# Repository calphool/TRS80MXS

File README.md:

# TRS80MXS
TRS-80 Modular eXpansion System

This is repo is for the TRS-80 Modular eXpansion System (MXS).  The intent is to make it the final of a series of 
prototypes (TRS80HDD and TRS80GS and a memory expansion module).  

The MXS consists of four modules set up as a stackable set.  So, you can build the base module first, which will 
give you a 32k memory expansion for your TRS-80 Model 1, as well as a power conditioning base that the other boards
use.  Then you can make either the floppy drive emulator, the TI video/graphics board, or the WIFI board (or all three).  
The boards snap together.  

Theory of Operation
===================

The basic theory of operation of the MXS is covered in the other projects in this repo.  The combined unit has a few 
unique characteristics.  First, it has three headers at the north, and south positions, and northeast of each board.  These 
are what allow the boards to be stacked.  One header is mostly the address bus of the TRS-80 expansion connector, 
passed through a 74LS244 buffer.  It also includes the operation signals (RD, WR, IN, OUT).  The opposite header 
contains the data bus and a few miscellaneous signals.  Finally the header at the northeast position is 4 lines that 
are OR-ed into the WAIT* signal as well as another 4 that are tied into the INTERUPT* signal.  This allows the 
MXS to host 4 separate chips that might use the WAIT* mechanism (as the sound chips and the floppy emulator 
flip flop do), and 4 interrupt chips (which presently are only used by the floppy emulator for its clock and 
drive activity interrupts).  The floppy emulator board also includes an 8x2 header that consolidates all the 
unused Teensy signals as well as a ground, 5V, and 3.3V signal.  These pins can be utilized to extend the functionality
of the Teensy unit.

Build Notes
===========

September 21, 2020

I've been fooling around with a few more designs recently.  Someone asked me if I had considered building a stand alone joystick board.
I had never considered it, but I went ahead and put two together.  One supports two joystick ports, and allows you to select the port 
numbers with dip switches.  The other is bare bones.  It only supports one joystick, but it can be built for somewhere between $15 and $30.

I also stumbled on a weird bug in the Teensy code for the floppy emulator.  When you swapped the disk image, every once in a while the 
TRS-80 would either lock up or show random garbage on the screen.  It looks like it's some kind of weird timing bug, most likely because 
the SD drive emulation is a little slow, and the code was leaving the WAIT signal low while the entire mount command was active.  So I 
tweaked a couple of things to fix that.

Also, just a quick note.  Jan Beta did a [Septandy video](https://www.youtube.com/watch?v=hyTF-FG4Bv8) where he's working on a Model 1.  He
didn't have a power supply for it, so he built one.  As I was watching the video, he briefly pulls out the schematic of the power supply, and 
I was like "Hey, that's *MY* power supply design!"  Unfortunately, he ends up losing a bunch of time in his debugging exercise because he 
didn't have one of the center tap lines connected correctly.  Incidentally, the way he constructed his power supply looks a lot more 
professional than mine.  I just threw mine in an electrical gang box, but his looks like it has a nice case and everything.

June 28, 2020

I updated the graphics/sound board again.  This time I made it so that the joystick ports are compatible with the "Alphastick" joystick
that was sold back in the early 1980s.  Several games support this joystick.  Also, I added a pair of jumpers that switches between the two 
different kinds of joystick trigger modes supported on these old joystick designs.  

I also learned how to use graphics mode 2 to produce near-bitmap style graphics.  So, I created a start-up screen for the MXS board that runs 
as soon as NewDos/80 loads up.

I finished the Pac-Man clone.  Now I've started on a Joust clone.  Joust runs in graphics mode 2, which makes for amazingly accurate reproduction of the 
background.  I've been working on the SDL emulation layer so that I can duplicate the TMS9918's "only 4 sprites per scanline" behavior.  I need to
duplicate this behavior so that I can come up with a "flicker routine."  This was the approach used for TMS9918 games back in the day.  You 
detect the situation, and then rotate the sprites' priorities in order to make sure that no one sprite turns off completely.

So I'm at version 1.4 of the graphics/sound board.  It's done and working well.  I have given some thought to removing two of the sound chips 
(do I really need 12 voices?  6 seems like it ought to be adequate), and replacing them with a TMS5220 speech synthesis chip.  This would make the 
board quite versatile.  Though the TMS5220 has become difficult to find, so I'm not sure.  I'll probably finish the Joust clone first.

May 9, 2020

Well, with the pandemic I've had a little time to work on the project some more.  I haven't worked on the wifi board recently,
but I decided to put together at least one piece of software that demonstrates the graphics/sound/gaming capabilities of the 
TRS80MXS.  [Here's a little video of the Pac-Man clone.](https://youtu.be/DzdaCiHI2xc)  It's a work in progress, but it's at least starting to look like a playable game.

January 1, 2020

Well, we're in the new house, and semi-settled.  Always a million things to do when you move to a new house.  
However, I've got a little time to begin working on the Wifi module again.  As luck would have it, I'm now living 
only a few blocks from my friend who started this little adventure.  Just for fun over Christmas, I had my younger 
daughter come play some of the games that are loaded on the HDD module.  I even hooked up the cassette port to 
an amplifier, and I connected the composite video out on my old TRS-80 to our big screen TV.  It's kind of 
amazing when you think about it -- that computer is 42 years old, and I can connect it to a brand new flat panel display.
My daughter laughed her head off at these "cheesy old games."  She said something like "Dad, how could you guys 
stand to play these silly things?  There's no color. They're like really bad rip offs of arcade games that weren't 
that great to begin with!"  The answer of course is pretty simple.  We had no choice, and we *thought* they were 
pretty cool games.  In fact, I'm still pretty amazed when I ran a couple of those games and the authors had managed 
to implement a sample playing routine into the game so that when it started it said something like "Ready Player One" 
and "Game Over".  I mean, seriously -- in 1977 somebody had figured out how to sample audio and misuse the audio 
cassette port to drive voice samples.  It may not be impressive to my 20 something daughter, but it's still pretty 
impressive to me.  Perspective I guess.

So I'll see if I can wrap up the Wifi module in the next few weeks.  It was intended to be a general purpose 
wifi module, but I'm running into some things that make me think that may not be practical / easy.  The main one is 
that the ESP32 designers didn't really imagine that someone would use their module for a general purpose HTTP client.
The issue is basically RAM constraints.  We take it for granted these days, but TLS security requires a *lot* of 
RAM to store a bunch of root certificates.  The code that implements the TLS stuff for my ESP32 module makes a 
rather huge assumption that you're going to have a single site that the module is going to talk to, so you don't
really even try to load a bunch of root certs into it.  You load one for the site your're going to be accessing.
That obviously doesn't work very well when you're trying to build a general purpose tool.  Now I *could* probably
implement a proxy in AWS or something, and then set up my ESP32 to work against that HTTP proxy, but I don't really 
want this hardware to be a slave to some stupid proxy running in AWS.  So, I'm at a bit of an impass.  I *may* be 
able to figure something out, but it'll require me to dig deeply into the TLS libraries for my ESP32, and basically 
rewrite a huge chunk of their code.... and who knows what the performance will be like.  The other possible route 
would be to do something like reduce the functionality of the Wifi module so that it just gives you access to a 
particular hosting site, like maybe DropBox, but that's a bit of a let down.  We'll see what I can come up with 
over the next few weeks.

October 21, 2019

I'm still working on the project.  Things have slowed down a bit over the past few months because my eldest daughter got married, 
my youngest daughter started college, and I'm selling my house.  Once I get settled in the new house I'll pick up the 
Wifi module again, which is the last one to get completely working.  It "sort of" works right now, but it's built around the 
ESP32 module and that thing is sort of a bugger to code for.

July 25, 2019

I purchased a TRS-80 Model 1 on Ebay, so I don't have to borrow my friend's any more.  Unfortunately, it didn't come with a 
power supply.  So, I designed one.  Maybe someone with a bad power supply can use my design.  Here's a pic of the [schematic.](img/powersupply.pdf?raw=true)
The schematic and board layout is in the eaglecad folder.  I didn't actually use the board layout.  I just hand wired everything for my supply, and put it 
inside an electrical utility box.  If you decide to make one of these, be very careful.  You'd working with 110V mains voltages, so you need to know what 
you're doing.  I'm not responsible if you electrocute yourself!)

July 7, 2019

Figured something out that's worth documenting.  For a long time I've thought that something was wrong with drive 3.  I was 
using NEWDOS/80 2.0 disk images in drive 0 (boot drive).  Apparently there's a command (PDRIVE) that changes how DOS handles
different drives.  The drive image I was using had the wrong settings for drive 3, and by dumb luck and coincidence had 
usable settings for the other 3 drives.  As soon as I changed drive 3's TI and TD settings, it started working properly, 
so there's nothing actually wrong with drive 3!

July 4, 2019

I just designed and uploaded the WIFI module.  It hasn't been built yet, and no software has been written, but the design is 
there.  I'll get the board and parts on order and see what we get.  Chances are it won't work right off the bat, but you 
never know.  I decided to design this board with a couple of nuances.  First, it is built around port IO rather than memory 
mapping.  Since the port numbers aren't really standardized on the TRS-80, I decided to make the address decoder selectable 
with 8 DIP switches, so any port between 0 and 255 can be chosen.  The other nuance is that I didn't use any GALs or CPLDs for 
the glue logic.  That should make this board a little easier to build than the graphics/sound board.

June 28, 2019

I wrote a utility (called "trs80mxs") that runs on the TRS-80 to manipulate the drive images that are stored on the MicroSD card.  Before this utility,
you had to do your manipulations from a Mac connected via USB.  Since that forced the MXS to be tethered, that didn't seem like a good long term solution.
So, I "stole" the address the TRS-80 uses for printers and turned it into a "general purpose communication buffer" between the Teensy and the TRS-80.  So,
the Teensy receives data, turns it into SD Card manipulation commands, and replies back with what happened.  So the trs80mxs command utility doesn't 
really do much -- it just sends commands to the printer address, and reads the response back through the same address, and prints it to the screen on 
the TRS-80.  With it you can list disk images that are on the SD card, mount them onto one of the 4 emulated drive slots, and list what is currently 
mounted.  I've also created a video of using the utility [here.](https://www.youtube.com/watch?v=PgaojUgeEG4)

June 16, 2019

I tweaked the Teensy code to support deleting and writing files now.  So now drives 1-3 work as perfect emulators for JV1 formatted files.  I still have no
idea why drive 4 acts flaky.  The code is literally identical.  It's got to be some bug in the Model 1 hardware behavior when you've got 4 floppies. I also
uploaded some more audio tools.  midiDump accepts a midi file and converts it to a large array that can be copy/pasted into one of the player files like 
bach.c and then compiled with z88dk to create a .cmd file.  It's a tiny bit buggy, but it more-or-less produces the right data.  One of these days I'll 
dig into what precisely is causing it to act a little flakey.

June 10, 2019

Improved the timing just a bit.  Hear the difference [here.](https://www.youtube.com/watch?v=ByLgBegGoTc)

May 31, 2019

I just uploaded a demo program that plays a J.S. Bach tune - Invention 13.  [Here's a video of it playing.](https://www.youtube.com/watch?v=8Pr8rdETvlA)  The player isn't 
quite perfect (some slight timing issues), but it's certainly recognizable.  I used a preprocessor that's located in the OSX code that reads a midi file and turns it into 
an array of structures.  This isn't quite ideal.  It would probably be better to merge the two so that the TRS-80 can directly play midi files.  I may go ahead and piece 
that together over the weekend if I can get the midifile cpp code to compile on z88dk (the compiler I'm using for the TRS-80).

May 27, 2019

I got some of the sound code working.  It took a while to figure out what was going on in playnote.c.  One of the big pains in 
the sound chips is that I wired the data lines backward due to strange labelling in the sound chip data sheets.  This requires 
you to think of the bits backward.  Anyway... got it working.  It's pretty cool hearing 12 simultaneous harmonious voices.

May 23, 2019

I am still using the previous version of the PCBs at this time.  I've removed one of the 7805 linear regulators and 
replaced it with a TRACO TSR2-2450 switching regulator.  It appears that the regulator is stable enough, which was one of 
the questions I had about those regulators.  It appears that they'll work okay.  I'll probably spend some time this weekend
working on software.  I'd like to get an audio demo up and working, then some video, and then I'll pivot to working on a 
wifi shield at some point in the near future.

April 21, 2019

I reworked the base board design and the graphics board design.  I'd added a switching supply for the 5V, but I left the 7805 in 
there as well, with a jumper to allow you to switch back and forth.  Since I don't know if the switching supply will be too noisy,
I figured I wanted to have something that I knew would work.  The reason I had to redesign the base power board was that I had 
some fuzzy thinking going on.  I had two 7805 regulators on the original board, with their outputs tied together.  For some reason
I was thinking that I could manage more current that way, but that's only true in a really crude and kind of useless way.  Basically
that configuration is a known antipattern.  What happens is the two 7805s sort of "fight" to see who's going to provide the 5V, one
wins, takes all the current, overheats, and then the other suddenly jumps in if its sibling's heat overload kicks in.  That's not 
really useable.  So instead, I figured I'd switch to a higher amperage switching circuit built around an LM2596.  Since I don't know
if the noise will be too much, I left one of the 7805s in place, and made it so you could use a jumper to switch between the two.  

All of that got me to thinking that maybe having a "regulator board" wasn't such a dandy idea anyway.  It forces all the current 
to be fed from that one board, which in turn creates a heat problem if I use linear regulators.  So, I also ran the raw 9V in to 
one of the previously unused header pins, which means that in future designs the shields could regulate their own power if need be.
I probably should swap out all the 74LS* chips for 74HCT* chips to reduce power consumption.  Save the planet man.  What are you 
doing with all these old power hungry chips?  (My experience has been that 74LS* chips are rock solid at the design stage, and then 
you can pivot to HCT or ACT later to get additional desirable qualities -- you just have to sort of "ease" them into your design 
to make sure you don't get caught with some unexpected behavior difference -- sometimes related to timing.)

Additionally, I added some inductors to the graphics board.  These are on the TI-99/4A schematics for the VDP, and presumably they're
there to stabilize power.  I noticed that the TI-99/4A circuits have several of these chokes throughout, and there's a clean 
separation between normal VCC and VCC for video, with the chokes being the main difference.  So far I haven't needed these, but 
I figure the TI engineers probably had them there for some reason.

I've been working on some audio software.  Soon I think I'll have a 12-part harmony audio player.  It's sort of like a MOD tracker
from back in the day, but it doesn't play samples -- just manipulates the tone generators on the sound chips.  I'm anxious to 
get it working fully so I can try out some stuff.  I'll probably build some kind of midi converter as well.  Interestingly 
enough I haven't yet been able to find a midi file that tries to use 12 voices at once.  I wrote a little utility that calculates 
tone depth across all midi channels, ran hundreds of midi files through it, and so far I've only been able to find one song with 
more than 10 simultaneous voices, so 12 tonal voices might have been overkill.  Oh well.  ;-)

April 13, 2019

Got the third board working.  Getting the GAL22V10D programmed ended up being a pain.  I don't know why, but my VS4800 programmer just decided 
it wasn't going to program my ATF22V10C chips, so I bought some GAL22V10D chips.  It wouldn't program them either.  So, I decided to install VSpeed
(the programmer software) on another machine, and although at first it did the same thing, after fooling around over and over again (using the "all compare" function seemed to somehow cause it to start working).  One thing I can say for sure using that software and programmer is that until you issue the program instruction followed by a Read IC instruction and the checksum matches, you haven't programmed it properly.  You can also avoid the encrypt function, because it introduces its own chaos into the mix.  I suppose if I had an expensive programmer I wouldn't have to deal with that nonsense.

So, today is basically the culmination of a lot of hard work for a long time.  Today I should be able to write code on my Mac, create a disk image with trstools, sneakernet that code over a microSD card to my floppy emulator or upload it via USB to the teensy, and now I've got 12 channel audio and graphics (and of course 32k of extra ram on the power distribution board).  I'll go through a few cycles of that in the next few days to prove that it works, maybe create a build pipeline for my pacman game.  

I'll decide after I get a few rounds of that under my belt if I want to design/build one more shield board -- an ESP32 board.  This would give the system 
one additional feature that could be pretty useful -- wireless connectivity.  For my build pipeline that would make it so I could skip the sneakernet 
step, do a compile on the computer and transfer wirelessly (maybe -- I would have to figure out how to get the data over to the teensy.  Maybe some transfer program that would move data from the ESP32 to the Teensy.)

March 17, 2019

Happy St. Patrick's Day!  Got the redesigned drive emulator "shield" working.  Last board is the video/sound board.  There's some LED weirdness going on with
the drive emulator board (probably pin reassignments or something), but I'm not going to fool around with that right now.  The drive emulation works as 
expected, so that's good enough.  Stay tuned for the final board.  It has the most dramatic changes, so it may take a little more debugging to get fully 
working.  Once it's done, then our layer sandwich is basically done, except for the wireless board that I haven't yet designed. 

In totally unrelated news, I bought an Apple IIGS for $250.  I don't have boot disks, so it tries to boot and then complains that it has nothing to 
boot from.  I've ordered some disks from ebay.  Gotta love the IIGS.  It was Woz's last serious involvement in engineering at Apple, and some argue that it 
saved the company because it extended the aging Apple II line just long enough for Apple's board to realize that Jobs didn't know what he was talking about 
trying to push the Mac line when the technology just wasn't there yet.  Some people slather a lot of praise on Jobs, and certainly he was a visionary, but
his visions were often too far ahead of what the technology could do at the time, which put the company at risk in the late 80s.  Vision is great and 
necessary, but engineering is where the rubber meets the road.  Any science fiction writer can imagine amazing technology.  Making it actually happen 
requires hard skills.

March 3, 2019

I got the first instance of the base board built and tested.  It had a bug in the RD*, WR*, IN*, and OUT* signal lines.  I just started using 
[busses in EagleCad](./img/bus.gif?raw=true), and the user interface is incredibly awkward.  It's *super* easy to accidentally combine bus lines in weird ways.  In my case 
I had combined the buffered and unbuffered copies of the RD*, IN*, OUT*, and WR* lines, and it was creating havoc.  Even after removing the 74LS244
that was supposed to be doing the buffering, it was still screwing stuff up.  So I had to cut several traces around the chip and wire it properly.
I updated the design in EagleCad (it's now version 1.1), but didn't send for new boards at this point.  If someone wants to buy a few of these things 
or something I'll go ahead and order some more.  [Here's a pic of the completed board](./img/TRS80MXS_Base_v1.0.jpg?raw=true)... well, mostly.  I didn't have a 3.3v regulator handy, so I left that off for now, easy enough to solder in later when needed.  I also didn't have 4.7k resistor networks of the right size, so I cobbled together a hand full of discrete resistors and made an array out of them.  It's not pretty, but it's functional for now.  I also modified a switch to be a right angle mounted switch, which is a little kludgy but it's stable and will be hidden in plastic at some point anyway.  So yeah, not beautiful, but completely functional and I'll be able to build the other two "shield" modules and snap them on there.  Next I'll get the floppy emulator moved into this new form factor and tested.

Oh yeah, talking to my friend about the project, he expressed that he'd like to be able to browse the web with his TRS-80.  That's a bit o a tall order, 
but in theory would be possible with one more "shield".  Namely, an ESP32-based shield that was interfaced in the same way that the floppy emulator is 
interfaced (with a memory location peep hole mapping via a flip-flop and some latches, along with a WAIT* pin to aid in timing.)  So yeah, I may do that 
as well.  That'd make for quite the [sandwich](./img/sandwich.jpg?raw=true) of boards (base + graphics/sound + ESP32 wifi + floppy if we want to use it more than once), but in principle it would work.  The hardest part would be the browser rendering engine itself.  It might be one of those projects where
you can get the skeleton of the thing working fairly easily (basic text handling like a Lynx or maybe Browsh browser), and then graphics and sound would require a lot of design, which can turn into someone else's labor of love if they want.

February 22, 2019

I received my PCBs the other day.  Unfortunately I didn't do a great job of carefully reviewing them before sending them to the fab house.  There are 
so many little things to check when you're making a PCB that it's easy to miss something.  In this case, I didn't double (and triple) check the 
orientation of the headers on the boards.  I had them oriented correctly on the base and the floppy emulator PCB, but I didn't have them right on the 
sound/graphics board.  So, I had to flip them (both horizontally and vertically... wow was I off!), and then move everything around on the board 
because all the traces were now too far away from their respective chips.  *sigh*.  Oh well, I'll remember next time.  So now that's done and I've 
got the graphics/sound board headed back to the fab house.  I wish I could get some kind of deal on the shipping.  The cost of the fabrication is 
nothing ($5 for five boards), but the shipping is $20.  I can start populating the base and floppy PCBs now, so I'll probably do that this weekend.  One
of the cool things about these boards is that by making them modular like this, I think I should be able to use them on other 8-bit computers... basically
the base board will be unique to each computer, but the sound/graphics and floppy emulator may be pretty close to just working as a "cartridge" in 
other 8-bit PCBs of the era.  Of course, they'll need different software, but I don't think it'll be a total overhaul to get them working with say 
an Apple II, Commodore, or Atari 8-bit.  We'll see.  I mean, there will be differences because those computers were built around a 6502 and these 
cards were built for a Z80 machine, but a lot still translates -- an address bus, an 8-bit data bus, and so on.  We'll see when we get there.  If I 
keep plugging away I'm sure we can figure out a way to create a set of semi-universal cards... though maybe that's more of a long term goal.

February 9. 2019

Found [this interesting diagram.](https://www.kguttag.com/wp-content/uploads/2017/11/198x-External-Video-by-KG.pdf)  It may be worth digging into this later.  It would be kind of cool to be able to merge the TRS-80 
video signal with the TMS9918 signal such that the TRS-80 signal is the back plane.

February 8, 2019

I decided to add two more sound chips to the graphics/sound shield.  So now there should be a grand total of 12 tonal voices
and 4 noise / drum voices.  That will make the sound card significantly more capable than it was before.  I also decided 
to add a divide-by-four circuit to the second set of sound chips' clock.  So, they'll play at exactly 1/4 the pitch of the other 
two sound chips, making the bottom attainable frequency something like 27hz, which is around the bottom A of a piano keyboard, 
thereby fixing one of the terminal annoyances of the SN76489, its ridiculously large range that unfortunately tends to 
start in the middle of the keyboard with the standard clock frequency.

In order to add the extra sound chips, some surgery was necessary on all three boards.  I needed to change the base board 
to accommodate more wait signals, which in turn meant that I needed to add an 8-input NAND, which in turn meant that the
4-input NANDs I was using before were sort of redundant.  So now there are 8 available interrupt lines and 8 wait lines, in a 
4x4 pin grid at the north east side of the board.  Five wait signals are being used now (4 for sound and one for the 
floppy drive).  One interrupt is being used by the floppy emulator, and I've made the video interrupt optional with a jumper.
I don't think that interrupt will ever be especially useful (since the floppy drive interrupt occurs 25 times a second 
anyway, we might as well just poll the video card for anything we need), so making it optional seemed smart.

In order to add the extra sound chips I had to dispose of the ability to issue a VDP reset from software (needed the pins 
on the CPLD).  Also, I had to reorder a couple of the pins on the CPLD because for some reason one of the pins couldn't handle the 
complexity of the logic equation I was feeding it.  (Wouldn't compile in WinCupl.)

I'm thinking maybe at some point I'll throw together a MIDI player for this sound card.  With 12 voices and a full keyboard range and 
then some, I should be able to play practically anything.  Who knows, maybe with a little clever programming I'll be able to get some 
different timbres and be able to handle MIDI program change messages even.  12-part audio is better than some polyphonic synthesizers, 
so this should be interesting.  The only concern I have is the amount of data I'd be jamming down the bus to accomplish anything interesting.
Each tone change is two OUT instructions, so to play 12 voices at the same time you'd be executing 24 instructions.  I'm not sure
if the time gap between the first note and the last will be audible or not.  I hope not.

So, now I think I'm about ready to send these things to a fab house.  

February 3, 2019

Completed design of all three units.  Now cross checking them and preparing them for production at allpcb.com.

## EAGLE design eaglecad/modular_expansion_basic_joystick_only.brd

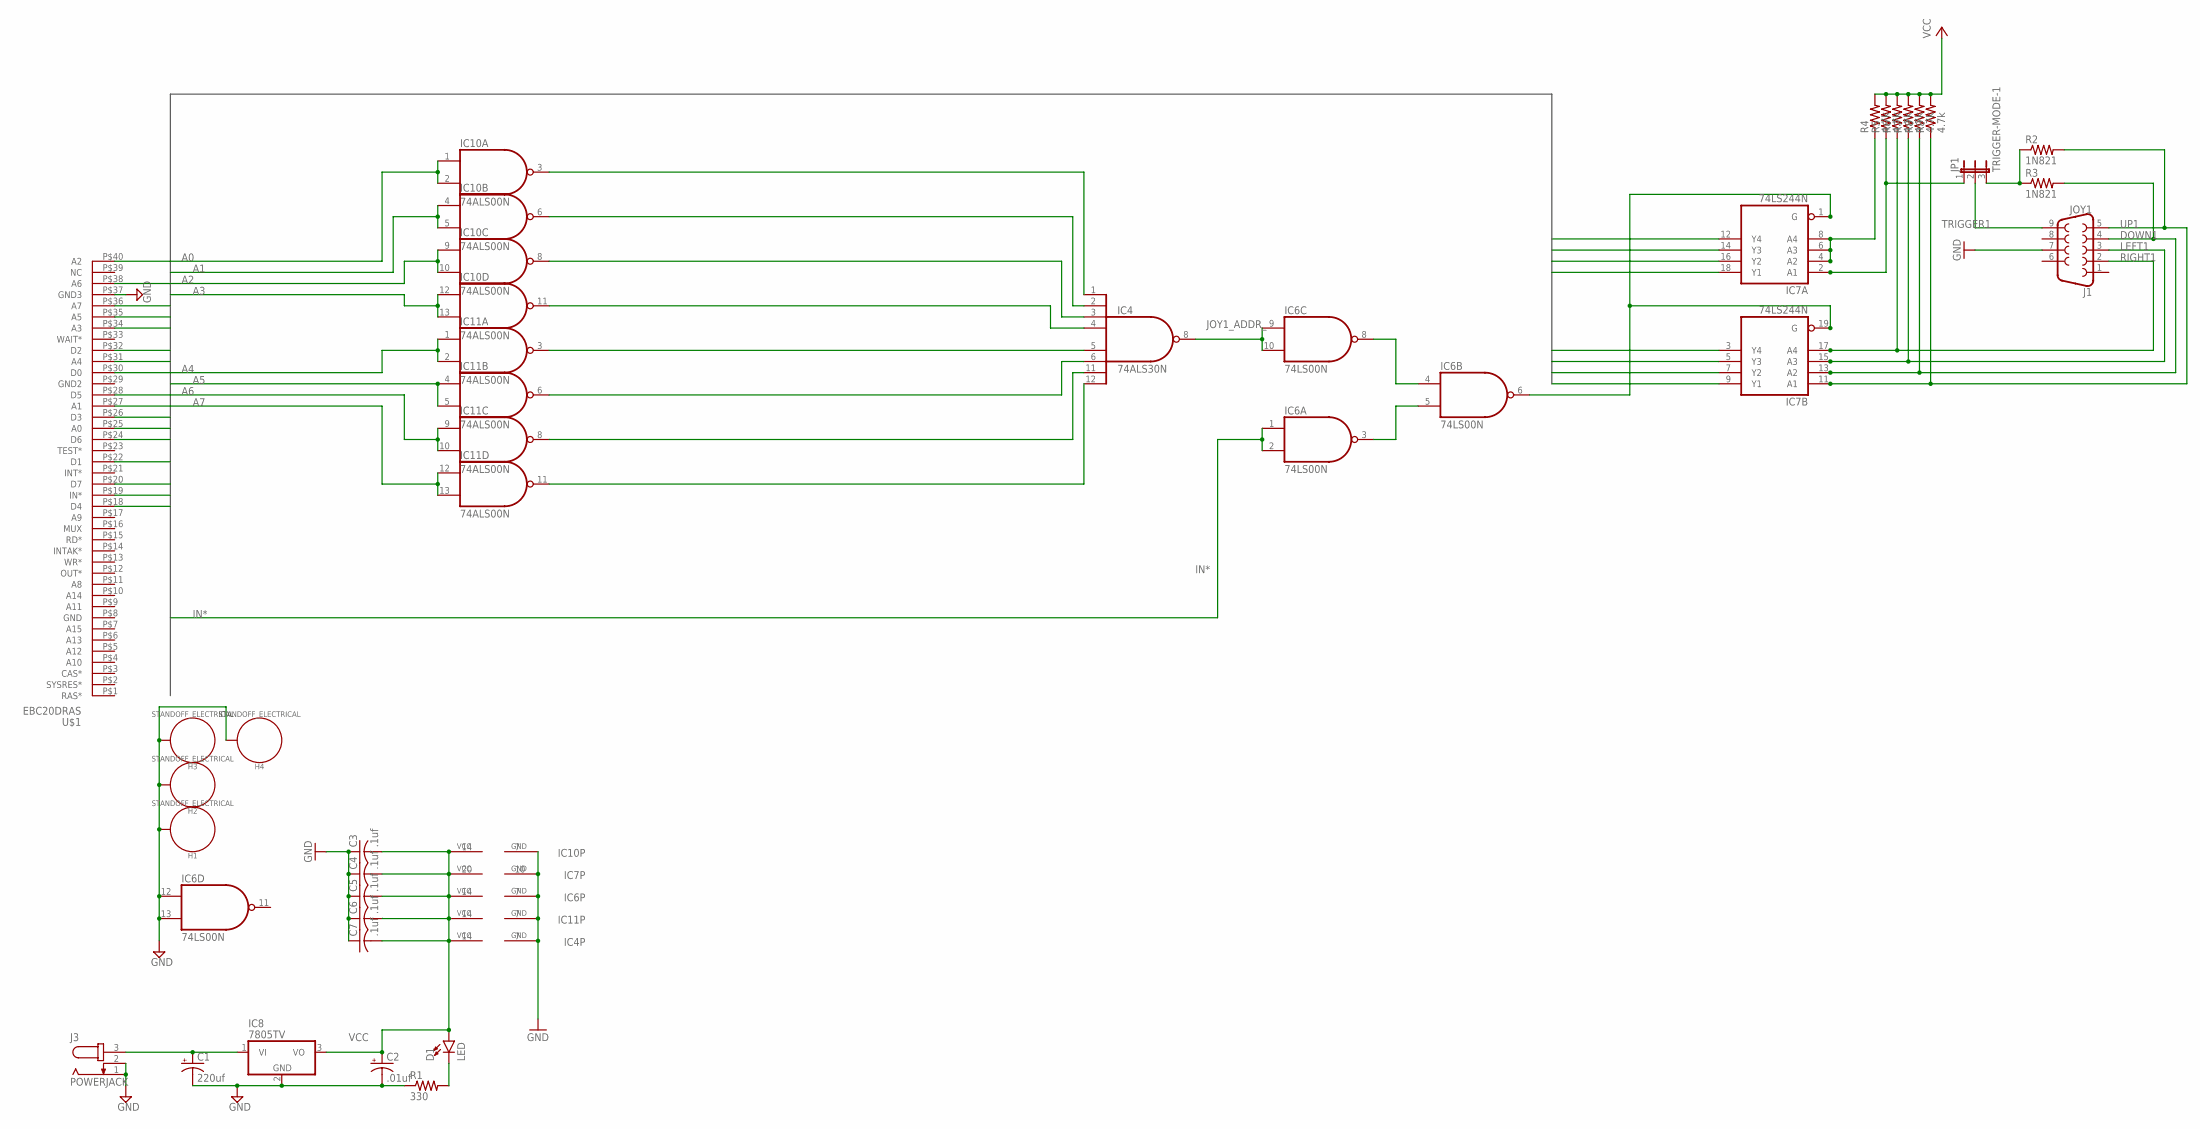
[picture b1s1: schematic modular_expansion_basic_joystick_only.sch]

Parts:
C1: 220uf; E3,5-10
C2: .01uf; E2,5-6E
C3, C4, C5, C6, C7: .1uf; C025-025X050
D1: LED; LED_3MM
H1, H2, H3, H4: STANDOFF_ELECTRICAL; STANDOFF-ELECTRICAL
IC4: 74ALS30N; DIL14
IC6: 74LS00N; DIL14
IC7: 74LS244N; DIL20
IC8: 7805TV; TO220V
IC10, IC11: 74ALS00N; DIL14
J1: JOY1; DB9
J3: POWERJACK; SPC4077
JP1: TRIGGER-MODE-1; JP2
R1: 330; 0204V
R2, R3: 1N821; 0204V
R4, R5, R6, R7, R8, R9: 4.7k; 0204/5
U$1: EBC20DRAS

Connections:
A0: IC10.1 (I0), IC10.2 (I1), U$1.P$25 (A0)
A1: IC10.4 (I0), IC10.5 (I1), U$1.P$27 (A1)
A2: IC10.9 (I0), IC10.10 (I1), U$1.P$40 (A2)
A3: IC10.12 (I0), IC10.13 (I1), U$1.P$34 (A3)
A4: IC11.1 (I0), IC11.2 (I1), U$1.P$31 (A4)
A5: IC11.4 (I0), IC11.5 (I1), U$1.P$35 (A5)
A6: IC11.9 (I0), IC11.10 (I1), U$1.P$38 (A6)
A7: IC11.12 (I0), IC11.13 (I1), U$1.P$36 (A7)
D0: IC7.9 (Y1), U$1.P$30 (D0)
D1: IC7.7 (Y2), U$1.P$22 (D1)
D2: IC7.5 (Y3), U$1.P$32 (D2)
D3: IC7.3 (Y4), U$1.P$26 (D3)
D4: IC7.18 (Y1), U$1.P$18 (D4)
D5: IC7.16 (Y2), U$1.P$28 (D5)
D6: IC7.14 (Y3), U$1.P$24 (D6)
D7: IC7.12 (Y4), U$1.P$20 (D7)
DOWN1: IC7.13 (A2), J1.4, R3.2, R8.1
GND: C1.-, C2.-, C3.1, C4.1, C5.1, C6.1, C7.1, H1.P1, H2.P1, H3.P1, H4.P1, IC4.7 (GND), IC6.7 (GND), IC6.12 (I0), IC6.13 (I1), IC7.10 (GND), IC8.2 (GND), IC10.7 (GND), IC11.7 (GND), J1.7, J3.1, J3.2, R1.1, U$1.P$37 (GND3)
IN*: IC6.1 (I0), IC6.2 (I1), U$1.P$19 (IN*)
JOY1_ADDR_: IC4.8 (O), IC6.9 (I0), IC6.10 (I1)
JOY1_SELECTED_: IC6.6 (O), IC7.1 (G), IC7.19 (G)
LEFT1: IC7.15 (A3), J1.3, R7.1
unnamed: IC4.5 (I4), IC11.3 (O)
unnamed: IC4.1 (I0), IC10.3 (O)
unnamed: IC4.6 (I5), IC11.6 (O)
unnamed: IC4.11 (I6), IC11.8 (O)
unnamed: IC4.2 (I1), IC10.6 (O)
unnamed: IC4.3 (I2), IC10.8 (O)
unnamed: IC4.12 (I7), IC11.11 (O)
unnamed: IC4.4 (I3), IC10.11 (O)
unnamed: IC6.4 (I0), IC6.8 (O)
unnamed: IC6.3 (O), IC6.5 (I1)
unnamed: C1.+, IC8.1 (VI), J3.3
unnamed: JP1.3, R2.1, R3.1
unnamed: D1.K (C), R1.2
unnamed: IC7.4 (A2), IC7.6 (A3), IC7.8 (A4), R4.1
unnamed: IC7.2 (A1), JP1.1, R5.1
RIGHT1: IC7.17 (A4), J1.2, R6.1
TRIGGER1: J1.9, JP1.2
UP1: IC7.11 (A1), J1.5, R2.2, R9.1
VCC: C2.+, C3.2, C4.2, C5.2, C6.2, C7.2, D1.A, IC4.14 (VCC), IC6.14 (VCC), IC7.20 (VCC), IC8.3 (VO), IC10.14 (VCC), IC11.14 (VCC), R4.2, R5.2, R6.2, R7.2, R8.2, R9.2

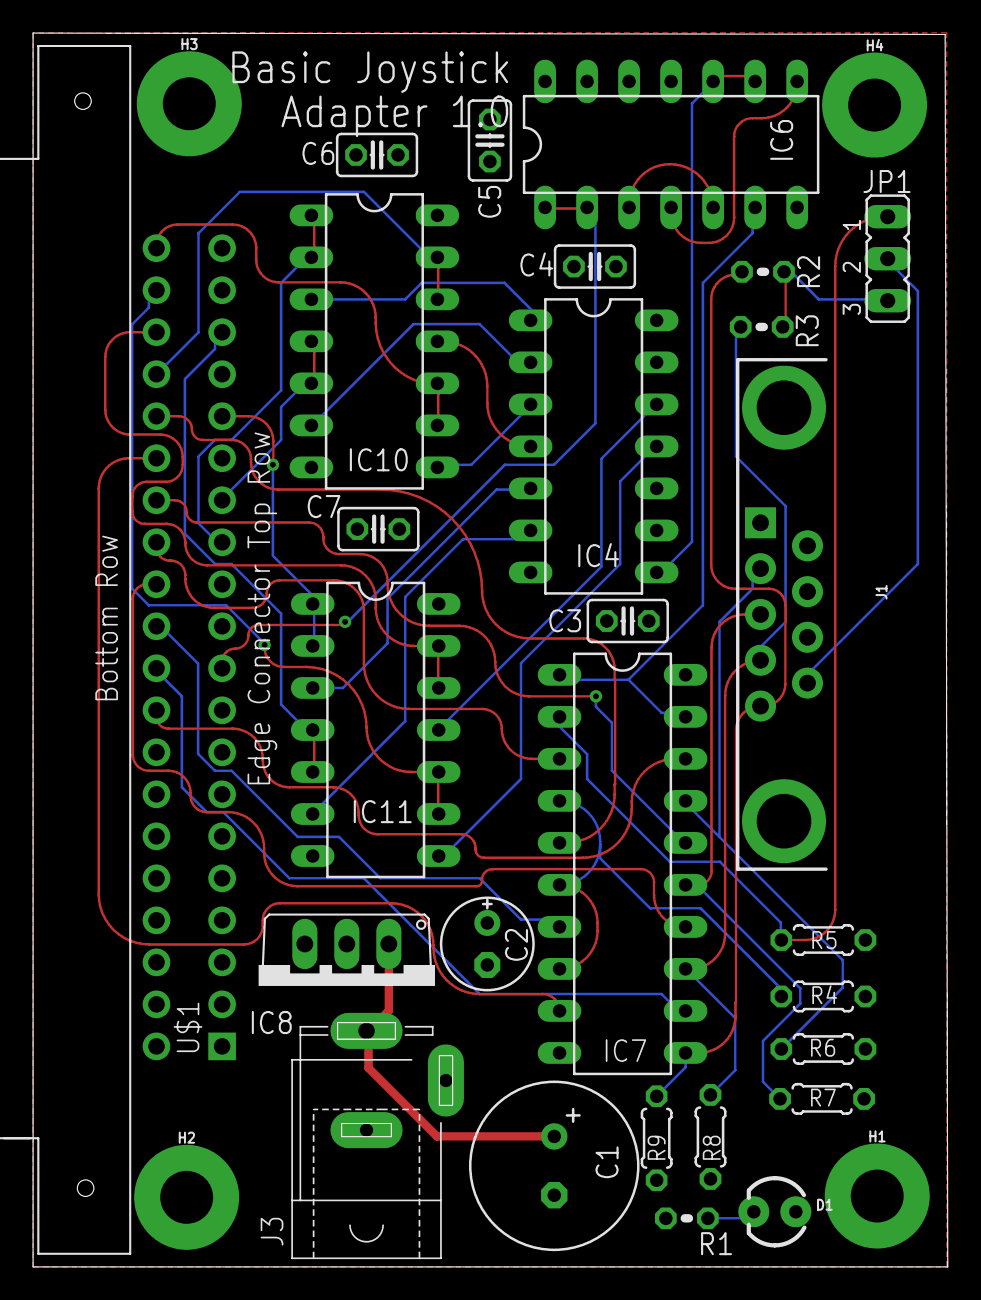
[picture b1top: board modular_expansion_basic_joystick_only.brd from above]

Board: 2 copper layers, 55.3 x 74.6 mm, 31 parts (0 on the bottom side), 41 nets.

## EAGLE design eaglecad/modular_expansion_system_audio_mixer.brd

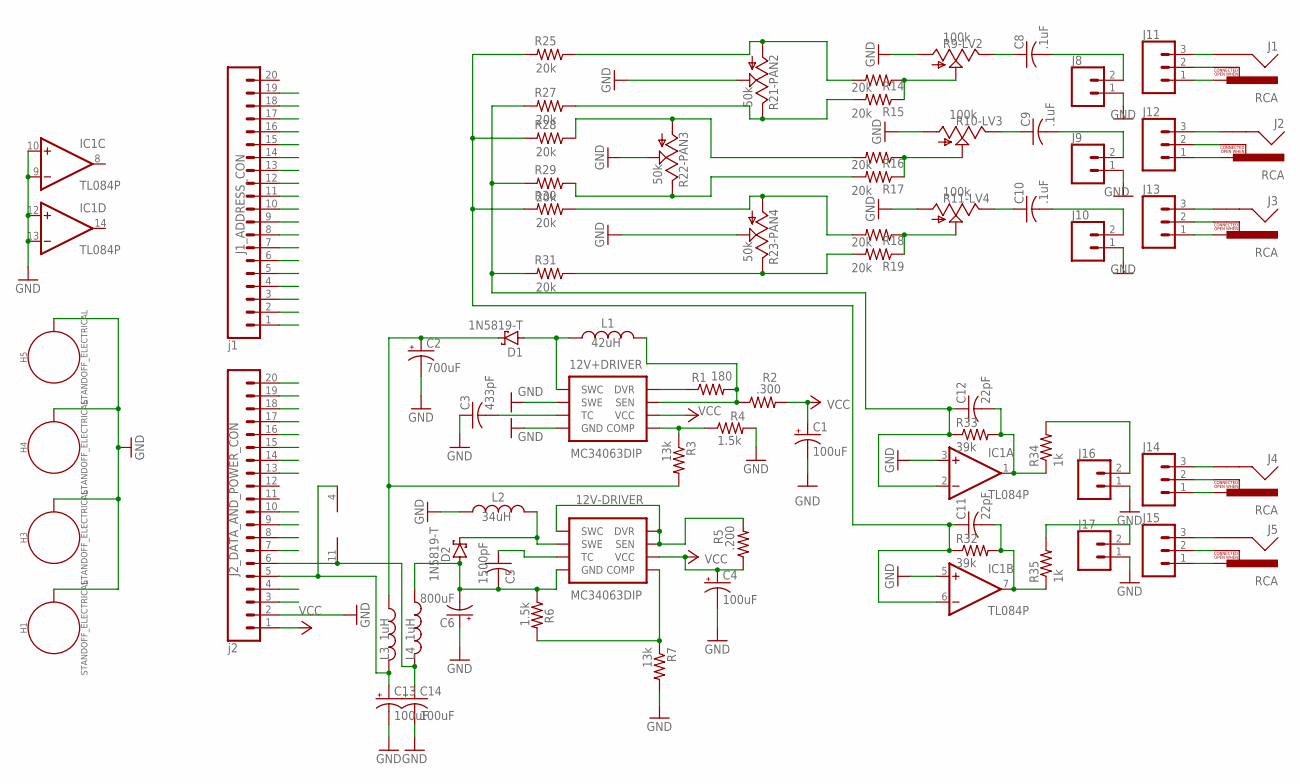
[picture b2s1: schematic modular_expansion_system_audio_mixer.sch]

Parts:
12V+DRIVER, 12V-DRIVER: MC34063DIP; DIP-08
C1, C4, C13, C14: 100uF; E2,5-5
C2: 700uF; E3,5-10
C3: 433pF; C025-040X050
C5: 1500pF; C025-040X050
C6: 800uF; E3,5-10
C8, C9, C10: .1uF; C025-024X044
C11, C12: 22pF; C025-024X044
D1, D2: 1N5819-T; DO41-7.6
H1, H3, H4, H5: STANDOFF_ELECTRICAL; STANDOFF-ELECTRICAL
IC1: TL084P; DIL14
J1, J2, J3, J4, J5: RCA
J1_ADDRESS_CON: j1; 1X20
J2_DATA_AND_POWER_CON: j2; 1X20
J8, J9, J10, J16, J17: CONN_02; 1X02
J11, J12, J13, J14, J15: CONN_03; 1X03
L1: 42uH; 0207/7
L2: 34uH; 0207/7
L3, L4: 1uH; 0207/5V
R1: 180; 0204V
R2: .300; 0204V
R3, R7: 13k; 0204V
R4, R6: 1.5k; 0204V
R5: .200; 0204V
R9-LV2, R10-LV3, R11-LV4: 100k; B25U
R14, R15, R16, R17, R18, R19, R25, R27, R28, R29, R30, R31: 20k; 0204V
R21-PAN2, R22-PAN3, R23-PAN4: 50k; B25U
R32, R33: 39k; 0204V
R34, R35: 1k; 0204V

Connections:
+12V: C2.+, D1.C, L3.1, R3.2
+12V_FILTERED: C13.+, IC1.4 (V+), J2_DATA_AND_POWER_CON.5, L3.2
-12V: 12V-DRIVER.4 (GND), C5.2, C6.-, D2.A, L4.1, R6.1
-12V-FILTERED: C14.+, IC1.11 (V-), J2_DATA_AND_POWER_CON.6, L4.2
A0: J1_ADDRESS_CON.1
A1: J1_ADDRESS_CON.2
A2: J1_ADDRESS_CON.3
A3: J1_ADDRESS_CON.4
A4: J1_ADDRESS_CON.5
A5: J1_ADDRESS_CON.6
A6: J1_ADDRESS_CON.7
A7: J1_ADDRESS_CON.8
A8: J1_ADDRESS_CON.9
A9: J1_ADDRESS_CON.10
A10: J1_ADDRESS_CON.11
A11: J1_ADDRESS_CON.12
A12: J1_ADDRESS_CON.13
A13: J1_ADDRESS_CON.14
A14: J1_ADDRESS_CON.15
A15: J1_ADDRESS_CON.16
CAS*: J2_DATA_AND_POWER_CON.9
D0: J2_DATA_AND_POWER_CON.20
D1: J2_DATA_AND_POWER_CON.19
D2: J2_DATA_AND_POWER_CON.18
D3: J2_DATA_AND_POWER_CON.17
D4: J2_DATA_AND_POWER_CON.16
D5: J2_DATA_AND_POWER_CON.15
D6: J2_DATA_AND_POWER_CON.14
D7: J2_DATA_AND_POWER_CON.13
GND: 12V+DRIVER.2 (SWE), 12V+DRIVER.4 (GND), C1.-, C2.-, C3.1, C4.-, C6.+, C13.-, C14.-, H1.P1, H3.P1, H4.P1, H5.P1, IC1.3 (+IN), IC1.5 (+IN), IC1.9 (-IN), IC1.10 (+IN), IC1.12 (+IN), IC1.13 (-IN), J2_DATA_AND_POWER_CON.2, J8.1, J9.1, J10.1, J16.1, J17.1, L2.1, R4.2, R7.2, R9-LV2.A, R10-LV3.A, R11-LV4.A, R21-PAN2.S, R22-PAN3.S, R23-PAN4.S
IN*: J1_ADDRESS_CON.17
INTAK*: J2_DATA_AND_POWER_CON.7
unnamed: 12V+DRIVER.8 (DVR), R1.1
unnamed: 12V+DRIVER.7 (SEN), L1.2, R1.2, R2.1
unnamed: 12V+DRIVER.1 (SWC), D1.A, L1.1
unnamed: 12V+DRIVER.3 (TC), C3.2
unnamed: 12V+DRIVER.5 (COMP), R3.1, R4.1
unnamed: 12V-DRIVER.1 (SWC), 12V-DRIVER.7 (SEN), 12V-DRIVER.8 (DVR), R5.2
unnamed: 12V-DRIVER.3 (TC), C5.1
unnamed: 12V-DRIVER.2 (SWE), D2.C, L2.2
unnamed: 12V-DRIVER.5 (COMP), R6.2, R7.1
unnamed: J3.SHELL, J13.3
unnamed: J3.SWITCH, J13.2
unnamed: J3.PIN, J13.1
unnamed: J2.PIN, J12.1
unnamed: J2.SWITCH, J12.2
unnamed: J2.SHELL, J12.3
unnamed: J1.SHELL, J11.3
unnamed: J1.SWITCH, J11.2
unnamed: J1.PIN, J11.1
unnamed: J4.SHELL, J14.3
unnamed: J4.SWITCH, J14.2
unnamed: J4.PIN, J14.1
unnamed: J5.SHELL, J15.3
unnamed: J5.SWITCH, J15.2
unnamed: J5.PIN, J15.1
unnamed: C8.1, R9-LV2.E
unnamed: C9.1, R10-LV3.E
unnamed: C10.1, R11-LV4.E
unnamed: C8.2, J8.2
unnamed: C10.2, J10.2
unnamed: C9.2, J9.2
unnamed: R9-LV2.S, R14.1, R15.1
unnamed: R10-LV3.S, R16.1, R17.1
unnamed: R11-LV4.S, R18.1, R19.1
unnamed: R14.2, R21-PAN2.A, R25.1
unnamed: R15.2, R21-PAN2.E, R27.1
unnamed: R16.2, R22-PAN3.A, R28.1
unnamed: R17.2, R22-PAN3.E, R29.1
unnamed: R18.2, R23-PAN4.A, R30.1
unnamed: R19.2, R23-PAN4.E, R31.1
unnamed: C11.1, IC1.6 (-IN), R25.2, R28.2, R30.2, R32.1
unnamed: C12.2, IC1.1 (OUT), R33.2, R34.1
unnamed: C12.1, IC1.2 (-IN), R27.2, R29.2, R31.2, R33.1
unnamed: C11.2, IC1.7 (OUT), R32.2, R35.1
unnamed: J16.2, R34.2
unnamed: J17.2, R35.2
OUT*: J1_ADDRESS_CON.18
RAS*: J2_DATA_AND_POWER_CON.10
RD*: J1_ADDRESS_CON.19
SYSRES*: J2_DATA_AND_POWER_CON.8
UNREG+: J2_DATA_AND_POWER_CON.4
VCC: 12V+DRIVER.6 (VCC), 12V-DRIVER.6 (VCC), C1.+, C4.+, J2_DATA_AND_POWER_CON.1, R2.2, R5.1
VCC/2: J2_DATA_AND_POWER_CON.3

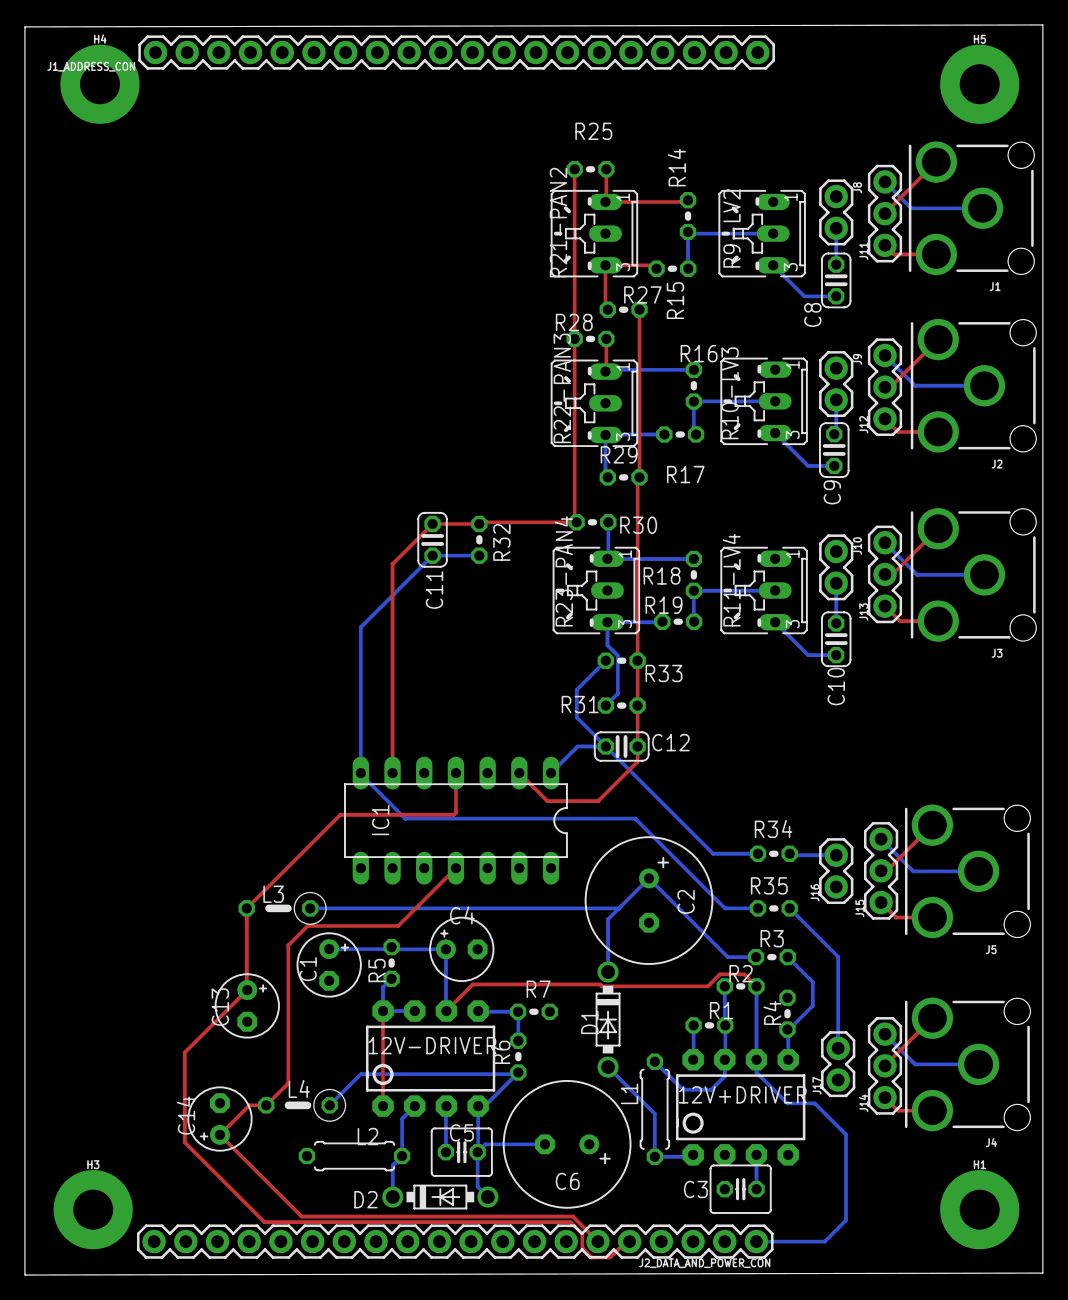
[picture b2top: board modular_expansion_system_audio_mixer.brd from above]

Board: 2 copper layers, 81.6 x 100.2 mm, 72 parts (0 on the bottom side), 51 nets.

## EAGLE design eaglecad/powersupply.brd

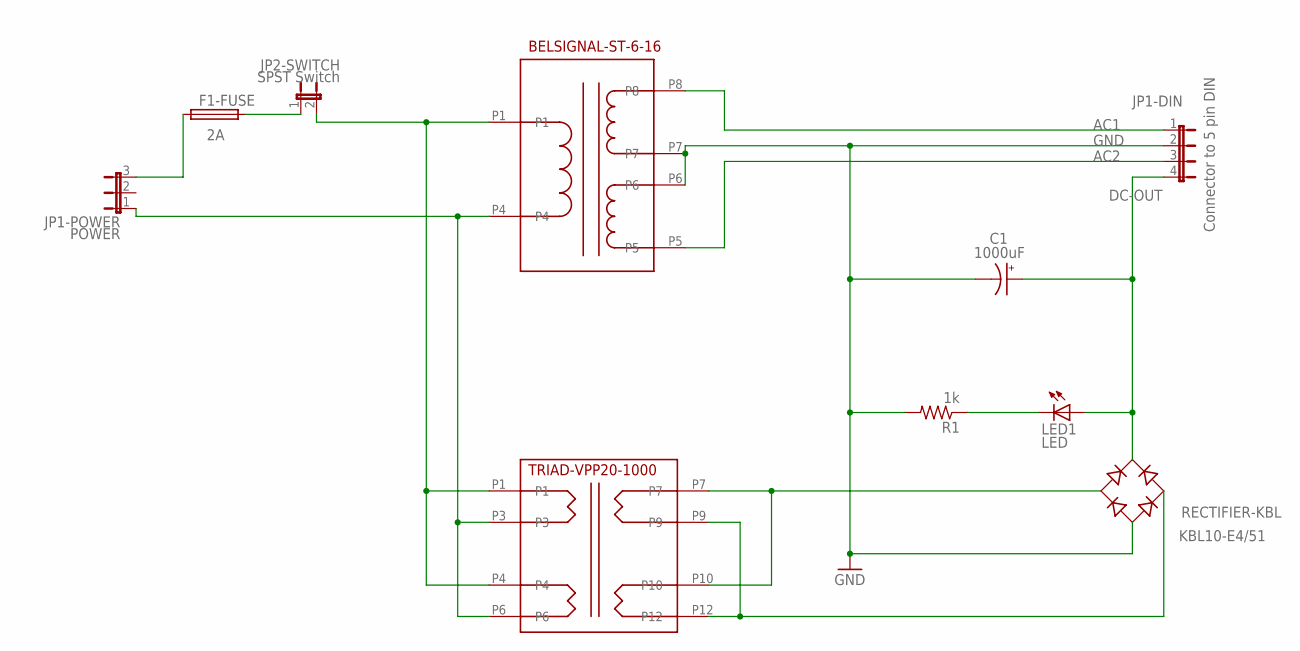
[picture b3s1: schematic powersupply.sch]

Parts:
BELSIGNAL-ST-6-16: ST-6-16
C1: 1000uF; E3,5-10
F1-FUSE: 2A; SH22,5
JP1-DIN: Connector to 5 pin DIN; JP4
JP1-POWER: POWER; JP2
JP2-SWITCH: SPST Switch; JP1
KBL10-E4/51: RECTIFIER-KBL; KBL
LED1: LED; LED5MM
R1: 1k; 0204/7
TRIAD-VPP20-1000: VPP20-1000

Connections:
AC1: BELSIGNAL-ST-6-16.P8, JP1-DIN.1
AC2: BELSIGNAL-ST-6-16.P5, JP1-DIN.3
AC-FOR-RECT-A: KBL10-E4/51.AC2, TRIAD-VPP20-1000.P9, TRIAD-VPP20-1000.P12
AC-FOR-RECT-B: KBL10-E4/51.AC1, TRIAD-VPP20-1000.P7, TRIAD-VPP20-1000.P10
AC-IN-2: BELSIGNAL-ST-6-16.P4, JP1-POWER.1, TRIAD-VPP20-1000.P3, TRIAD-VPP20-1000.P6
AC-IN-AFTER-FUSE: F1-FUSE.2, JP2-SWITCH.1
AC-IN-AFTER-SW: BELSIGNAL-ST-6-16.P1, JP2-SWITCH.2, TRIAD-VPP20-1000.P1, TRIAD-VPP20-1000.P4
AC-IN-BEFORE-FUSE: F1-FUSE.1, JP1-POWER.3
DC-OUT: C1.+, JP1-DIN.4, KBL10-E4/51.+, LED1.A
GND: BELSIGNAL-ST-6-16.P6, BELSIGNAL-ST-6-16.P7, C1.-, JP1-DIN.2, KBL10-E4/51.-, R1.2
unnamed: LED1.K (C), R1.1

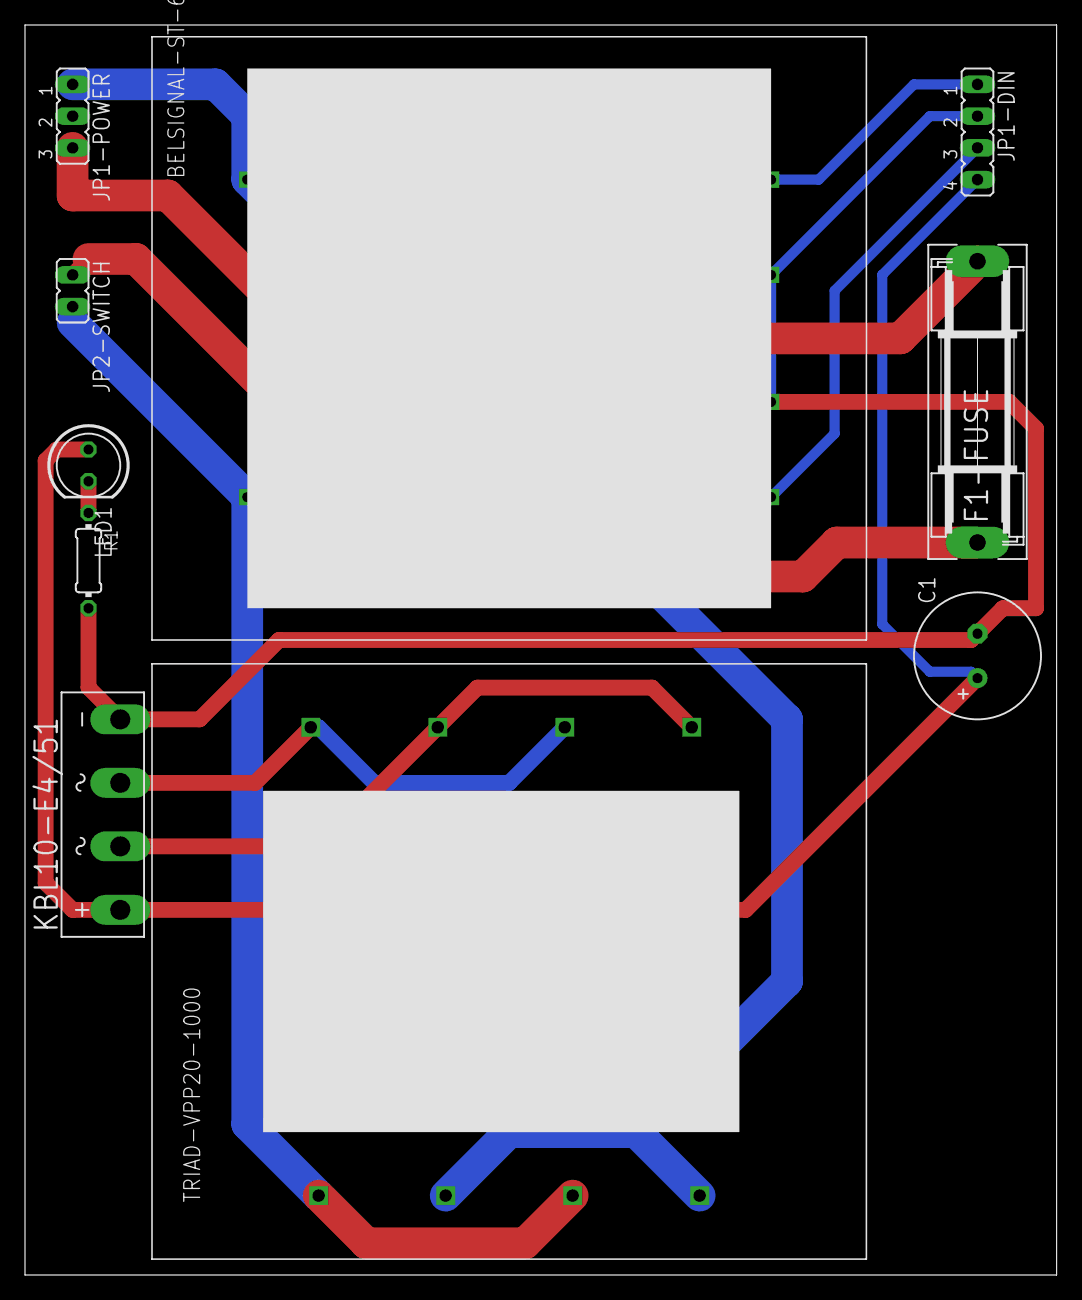
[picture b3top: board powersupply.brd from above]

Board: 2 copper layers, 82.5 x 100.0 mm, 10 parts (0 on the bottom side), 11 nets.

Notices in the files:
eaglecad/modular_expansion_system_base.brd:
Joe Rounceville (C) 2020
eaglecad/modular_expansion_system_floppy_emulator.brd:
Joe Rounceville (C)2019
parts and their libraries:
SparkFun-DiscreteSemi: Licensing: Creative Commons ShareAlike 4.0 International - https://creativecommons.org/licenses/by-sa/4.0
